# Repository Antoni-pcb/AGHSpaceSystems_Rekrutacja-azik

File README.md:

# AGHSpaceSystems_Rekrutacja-lazik

Yo, Zrobiłem zadanie 1.1. Układ mierzy prąd na zasadzie bocznika i układu INA240. Potem jest jeczcze zwykły wzmacbniacz operacyjny żeby dopasować output do 3V3. Zostawiłem na płytce miejsce na filtr. Jako że nie znam parametrów kontrolera który dostanie output to nie policzyłem konkretnych elementów.

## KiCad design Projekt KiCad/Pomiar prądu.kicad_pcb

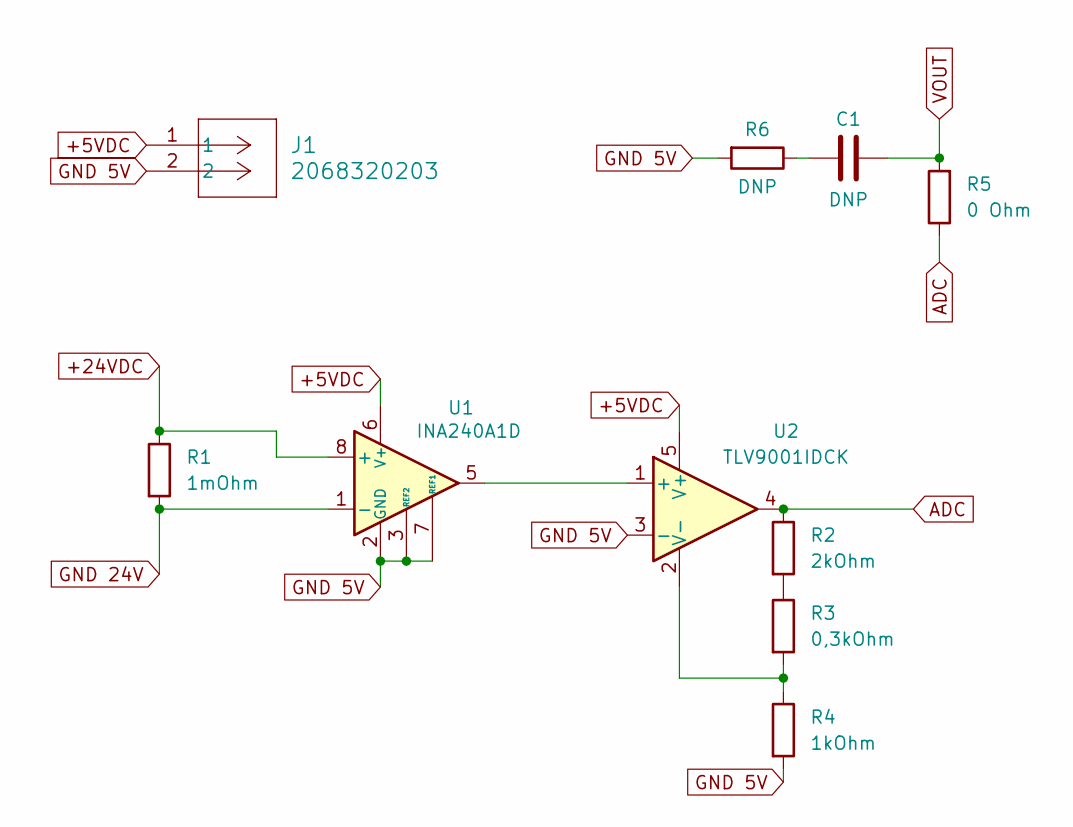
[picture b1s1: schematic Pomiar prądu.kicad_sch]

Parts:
C1: DNP; C_0603_1608Metric_Pad1.08x0.95mm_HandSolder
J1: 2068320203; CONN_2068320000-SD_02_MOL
R1: 1mOhm; 5930 Current Sense Resistor
R2: 2kOhm; R_0603_1608Metric_Pad0.98x0.95mm_HandSolder
R3: 0,3kOhm; R_0603_1608Metric_Pad0.98x0.95mm_HandSolder
R4: 1kOhm; R_0603_1608Metric_Pad0.98x0.95mm_HandSolder
R5: 0 Ohm; R_0603_1608Metric_Pad0.98x0.95mm_HandSolder
R6: DNP; R_0603_1608Metric_Pad0.98x0.95mm_HandSolder
U1: INA240A1D; SOIC-8_3.9x4.9mm_P1.27mm
U2: TLV9001IDCK; SOT-353_SC-70-5

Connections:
+5VDC: J1.1, U1.6 (V+), U2.5 (V+)
+24VDC: R1.1, U1.8 (+)
ADC: R2.1, R5.1, U2.4
GND 5V: J1.2, R4.2, R6.2, U1.2 (GND), U1.3 (REF2), U1.4 (GND), U1.7 (REF1), U2.3 (-)
GND 24V: R1.2, U1.1 (-)
unnamed: C1.1, R6.1
unnamed: R2.2, R3.1
unnamed: U1.5, U2.1 (+)
unnamed: R3.2, R4.1, U2.2 (V-)
VOUT: C1.2, R5.2

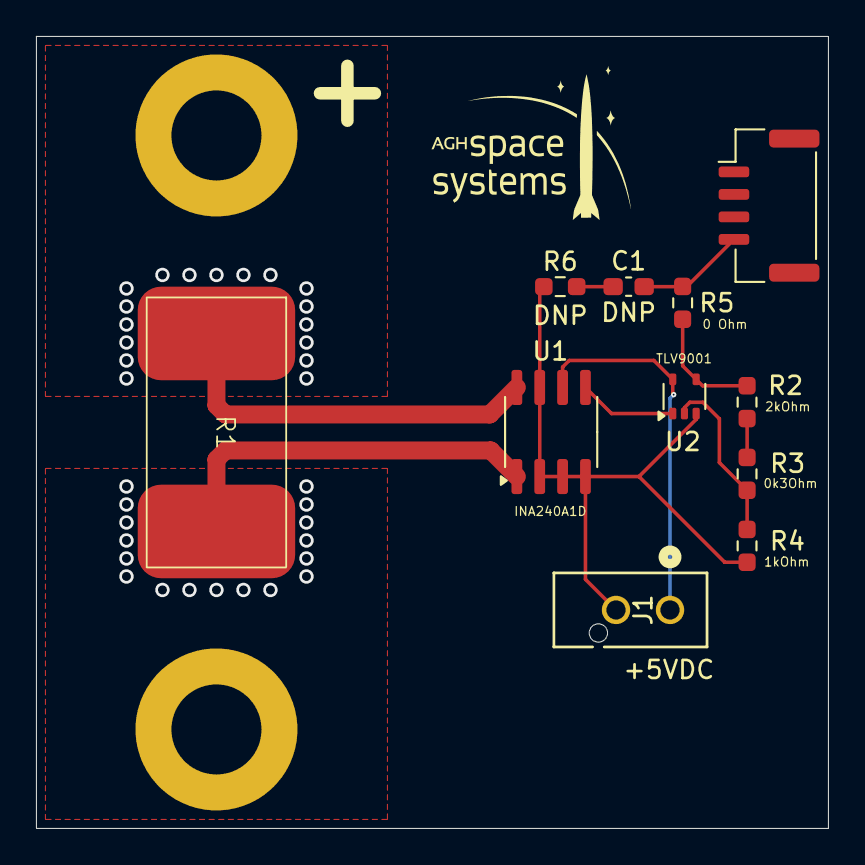
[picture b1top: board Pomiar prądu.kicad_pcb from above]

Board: 2 copper layers, 44.0 x 44.0 mm, 10 parts (0 on the bottom side), 10 nets.
